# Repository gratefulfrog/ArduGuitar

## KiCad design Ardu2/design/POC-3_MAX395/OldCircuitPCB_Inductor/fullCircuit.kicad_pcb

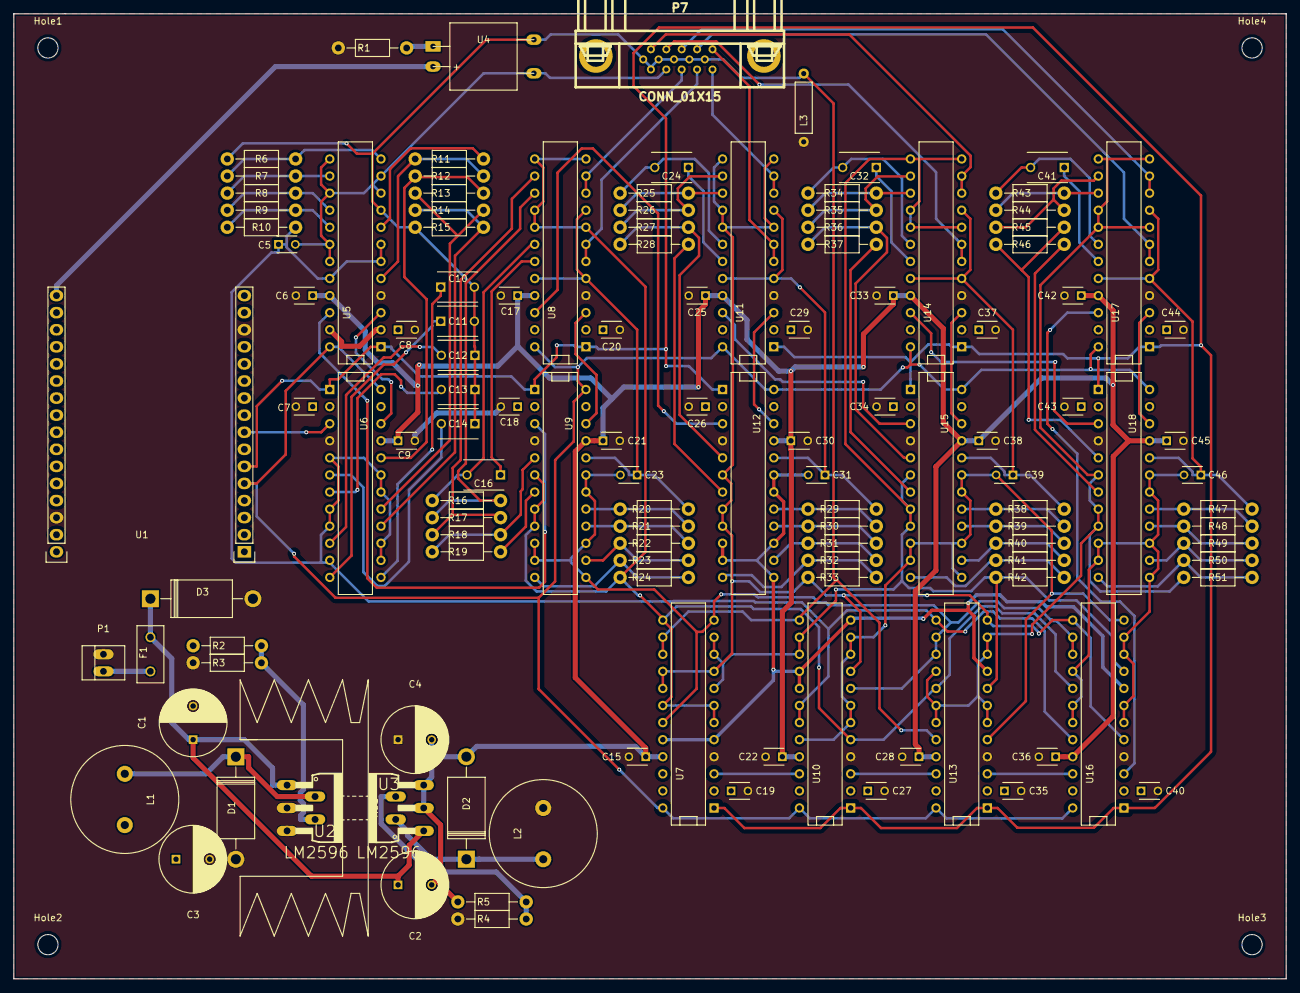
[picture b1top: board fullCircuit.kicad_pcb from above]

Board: 2 copper layers, 189.2 x 143.5 mm, 129 parts (0 on the bottom side), 104 nets.

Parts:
C1, C4: 470µF; C_Radial_D10_L16_P5
C2, C3: 220µF; C_Radial_D10_L16_P5
C5, C23, C31, C39, C46: 180pF; C_Disc_D3_P2.5
C6, C7, C8, C9, C15, C17, C18, C19, C20, C21, C22, C25, C26, C27, C28, C29, C30, C33, C34, C35, C36, C37, C38, C40, C42, C43, C44, C45: 100nF; C_Disc_D3_P2.5
C10, C16, C24, C32, C41: 10nF; C_Disc_D6_P5
C11: 6.8nF; C_Disc_D6_P5
C12: 4.7nF; C_Disc_D6_P5
C13: 2.2nF; C_Disc_D6_P5
C14: 1nF; C_Disc_D6_P5
D1, D2, D3: 1N5401; Diode_DO-201AD_Horizontal_RM15
F1: FUSE; Fuse_TE5_Littlefuse-395Series
HS1: HEATSINK; Heatsink_TO_220_38_20
Hole1, Hole2, Hole3, Hole4: MountingHole_3mm
L1, L2: INDUCTOR; 330L-Q9N_Inductor
L3: 1mH; Inductor
P1: CONN_01X02; PINHEAD1-2
P7: CONN_01X15; DB_15F-VGA
R1: 220; Resistor_Horizontal_RM10mm
R2, R4: 1K; Resistor_Horizontal_RM10mm
R3, R5: 330; Resistor_Horizontal_RM10mm
R6, R7, R8, R9, R10, R20, R21, R22, R23, R24, R29, R30, R31, R32, R33, R38, R39, R40, R41, R42, R47, R48, R49, R50, R51: 100K; Resistor_Horizontal_RM10mm
R11, R19, R28, R37, R46: 62K; Resistor_Horizontal_RM10mm
R12, R18, R27, R36, R45: 33K; Resistor_Horizontal_RM10mm
R13, R14, R16, R17, R25, R26, R34, R35, R43, R44: 16K; Resistor_Horizontal_RM10mm
R15: 22K; Resistor_Horizontal_RM10mm
U1: Pyboard; Pyboard16x2
U2, U3: LM2596; T05D
U4: Vactrol
U5, U6, U7, U8, U9, U10, U11, U12, U13, U14, U15, U16, U17, U18: MAX395; DIP-24__300

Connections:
/A+: P7.14, U17.6, U17.7
/A-: P7.13, U17.10, U17.11
/AOut+: C46.2, U16.6, U16.7, U16.10, U16.11, U16.16, U16.18, U16.19, U18.10, U18.11, U18.13, U18.15, U18.18, U18.19
/AOut-: R51.1, U13.6, U13.7, U13.10, U13.11, U13.16, U13.18, U13.19, U17.8, U17.12, U17.13, U17.16, U17.17, U18.6, U18.8, U18.9
/B+: P7.12, U14.6, U14.7
/B-: P7.11, U14.10, U14.11
/BATin: C1.1, C2.1, D3.1, F1.1, U2.1, U3.1
/BOut+: C39.2, U10.6, U10.7, U10.10, U10.11, U10.20, U13.5, U15.10, U15.11, U15.13, U15.15, U15.18, U15.19, U16.12
/BOut-: R42.1, U7.8, U7.10, U7.11, U10.14, U10.15, U13.8, U14.8, U14.12, U14.13, U14.16, U14.17, U15.6, U15.8, U15.9, U16.9
/C+: P7.15, U11.6, U11.7
/C-: P7.5, U11.10, U11.11
/CLK: U1.6, U5.1, U6.1, U7.1, U8.1, U9.1, U10.1, U11.1, U12.1, U13.1, U14.1, U15.1, U16.1, U17.1, U18.1
/COut+: C31.2, U7.5, U7.20, U10.12, U10.16, U10.17, U12.10, U12.11, U12.13, U12.15, U12.18, U12.19, U13.9, U16.8
/COut-: R33.1, U7.9, U7.16, U7.17, U10.9, U11.8, U11.12, U11.13, U11.16, U11.17, U12.6, U12.8, U12.9, U13.12, U16.5, U16.13
/CS: U1.5, U5.24, U6.24, U7.24, U8.24, U9.24, U10.24, U11.24, U12.24, U13.24, U14.24, U15.24, U16.24, U17.24, U18.24
/D+: P7.4, U8.6, U8.7
/D-: P7.3, U8.10, U8.11
/DOut+: C23.2, U7.12, U7.19, U9.10, U9.11, U9.13, U9.15, U9.18, U9.19, U10.8, U13.14, U13.15, U16.14, U16.15
/DOut-: R24.1, U7.6, U7.7, U7.13, U7.18, U8.8, U8.12, U8.13, U8.16, U8.17, U9.6, U9.8, U9.9, U10.5, U13.17, U16.17
/MIn+: C5.1, R10.2, U5.6, U5.7, U5.20, U6.5, U6.8, U6.9, U6.11, U6.14, U6.15, U6.18, U6.19, U10.18, U10.19, U13.13, U16.20
/MIn-: C10.2, C11.2, C12.1, C13.1, C14.1, L3.2, P7.1, P7.6, P7.7, P7.8, P7.9, P7.10, R6.1, R15.1, U4.3, U5.9, U7.14, U7.15, U10.13, U13.20
/OUT+: C5.2, P7.2, U4.4, U5.10, U5.11, U5.13, U5.15, U5.18, U5.19
/ShuntControl: U1.17, U4.2
/V+: C3.1, C7.1, C8.1, C18.1, C19.1, C20.1, C26.1, C27.1, C29.1, C34.1, C35.1, C37.1, C40.1, C43.1, C44.1, L1.2, R2.1, U1.16, U1.32, U5.2, U5.23, U6.2, U6.23, U7.2, U7.23, U8.2, U8.23, U9.2, U9.23, U10.2, U10.23, U11.2, U11.23, U12.2, U12.23, U13.2, U13.23, U14.2, U14.23, U15.2, U15.23, U16.2, U16.23, U17.2, U17.23, U18.2, U18.23
/V-: C2.2, C4.2, C6.1, C9.1, C15.1, C17.1, C21.1, C22.1, C25.1, C28.1, C30.1, C33.1, C36.1, C38.1, C42.1, C45.1, D2.2, R5.2, U3.3, U3.5, U5.21, U6.21, U7.21, U8.21, U9.21, U10.21, U11.21, U12.21, U13.21, U14.21, U15.21, U16.21, U17.21, U18.21
GND: C1.2, C3.2, C4.1, C6.2, C7.2, C8.2, C9.2, C15.2, C17.2, C18.2, C19.2, C20.2, C21.2, C22.2, C25.2, C26.2, C27.2, C28.2, C29.2, C30.2, C33.2, C34.2, C35.2, C36.2, C37.2, C38.2, C40.2, C42.2, C43.2, C44.2, C45.2, D1.2, D3.2, L2.2, L3.1, P1.2, R1.2, R3.2, R4.1, U1.14, U1.30, U2.3, U2.5, U5.4, U6.4, U7.4, U8.4, U9.4, U10.4, U11.4, U12.4, U13.4, U14.4, U15.4, U16.4, U17.4, U18.4
unnamed: C10.1, U6.13
unnamed: C11.1, U6.12
unnamed: C12.2, U6.10
unnamed: C13.2, U6.7
unnamed: C14.2, U6.6
unnamed: C16.1, U8.19
unnamed: C16.2, R16.1, U8.18
unnamed: C23.1, R20.2, U8.5, U8.9, U8.20, U9.20
unnamed: C24.1, U11.19
unnamed: C24.2, R25.1, U11.18
unnamed: C31.1, R29.2, U11.5, U11.9, U11.20, U12.20
unnamed: C32.1, U14.19
unnamed: C32.2, R34.1, U14.18
unnamed: C39.1, R38.2, U14.5, U14.9, U14.20, U15.20
unnamed: C41.1, U17.19
unnamed: C41.2, R43.1, U17.18
unnamed: C46.1, R47.2, U17.5, U17.9, U17.20, U18.20
unnamed: D1.1, L1.1, U2.2
unnamed: D2.1, L2.1, U3.2
unnamed: F1.2, P1.1
unnamed: R1.1, U4.1
unnamed: R2.2, R3.1, U2.4
unnamed: R4.2, R5.1, U3.4
unnamed: R6.2, R7.1, U5.12
unnamed: R7.2, R8.1, U5.14
unnamed: R8.2, R9.1, U5.16
unnamed: R9.2, R10.1, U5.17
unnamed: R11.1, R12.2, U5.5
unnamed: R11.2, U5.8
unnamed: R12.1, R13.2, U6.20
unnamed: R13.1, R14.2, U6.17
unnamed: R14.1, R15.2, U6.16
unnamed: R16.2, R17.1, U8.15
unnamed: R17.2, R18.1, U8.14
unnamed: R18.2, R19.1, U9.5
unnamed: R19.2, U9.7
unnamed: R20.1, R21.2, U9.17
unnamed: R21.1, R22.2, U9.16
unnamed: R22.1, R23.2, U9.14
unnamed: R23.1, R24.2, U9.12
unnamed: R25.2, R26.1, U11.15
unnamed: R26.2, R27.1, U11.14
unnamed: R27.2, R28.1, U12.5
unnamed: R28.2, U12.7
unnamed: R29.1, R30.2, U12.17
unnamed: R30.1, R31.2, U12.16
unnamed: R31.1, R32.2, U12.14
unnamed: R32.1, R33.2, U12.12
unnamed: R34.2, R35.1, U14.15
unnamed: R35.2, R36.1, U14.14
unnamed: R36.2, R37.1, U15.5
unnamed: R37.2, U15.7
unnamed: R38.1, R39.2, U15.17
unnamed: R39.1, R40.2, U15.16
unnamed: R40.1, R41.2, U15.14
unnamed: R41.1, R42.2, U15.12
unnamed: R43.2, R44.1, U17.15
unnamed: R44.2, R45.1, U17.14
unnamed: R45.2, R46.1, U18.5
unnamed: R46.2, U18.7
unnamed: R47.1, R48.2, U18.17
unnamed: R48.1, R49.2, U18.16
unnamed: R49.1, R50.2, U18.14
unnamed: R50.1, R51.2, U18.12
unnamed: U1.8, U6.3
unnamed: U5.3, U6.22
unnamed: U5.22, U9.3
unnamed: U8.3, U9.22
unnamed: U10.3, U13.22
unnamed: U7.3, U10.22
unnamed: U11.3, U12.22
unnamed: U11.22, U15.3
unnamed: U8.22, U12.3
unnamed: U13.3, U16.22
unnamed: U14.3, U15.22
unnamed: U14.22, U18.3
unnamed: U16.3, U17.22
unnamed: U17.3, U18.22
